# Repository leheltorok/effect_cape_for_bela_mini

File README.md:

# Effect Cape for Bela Mini

A programmable open-platform effect pedal based on the Bela framework.

The objective of this project is to create a customizable guitar effects pedal using Bela's embedded computing framework. The pedal  allows guitarists to design and run their own effects on dedicated audio hardware. To achieve this, an extension cape has been developed, integrating essential components such as rotary encoders, switches, and audio inputs/outputs onto a single circuit. Additionally, a software framework has been created using Pure Data, providing all the necessary functions for utilizing the device.

Demo Video:
https://www.youtube.com/watch?v=Ah0W3sH00xs&ab_channel=LehelTorok

## Authors and acknowledgment

Lehel Török - 2023

I would like to express my gratitude to the Bela team for providing exceptional tutorials and their invaluable support on the community forum. Additionally, I extend my thanks to the user community for generously sharing excellent code examples, which serve as a solid foundation for all of us to build upon.

## License

Creative Commons Attribution-NonCommercial-ShareAlike 4.0 International License
https://creativecommons.org/licenses/by-sa/4.0/

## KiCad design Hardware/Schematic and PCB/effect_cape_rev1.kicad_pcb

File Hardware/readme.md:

The circuit board was designed using KiCad, and manufactured with Eurocircuits. The cape was conceived as a stompbox incorporating four rotary encoders, each equipped with a switch, as well as two footswitches, all of which can be assigned based on personal preferences. The cape includes a 6.3 mm mono jack socket for audio input, two identical sockets for audio output, a 3.5 mm stereo jack socket for headphone output, and a 6.3 mm stereo jack socket for expression pedal input. In order to provide visual feedback for different modes, changes, and the status of each rotary encoder, both a bicolor LED and an OLED screen were integrated into the board. Additionally, to ensure compatibility with pedal board power supplies, a DC Barrel Jack was incorporated, enabling external power (5V/100mA) using 2.1 mm or 2.5 mm plugs with a negative polarity.

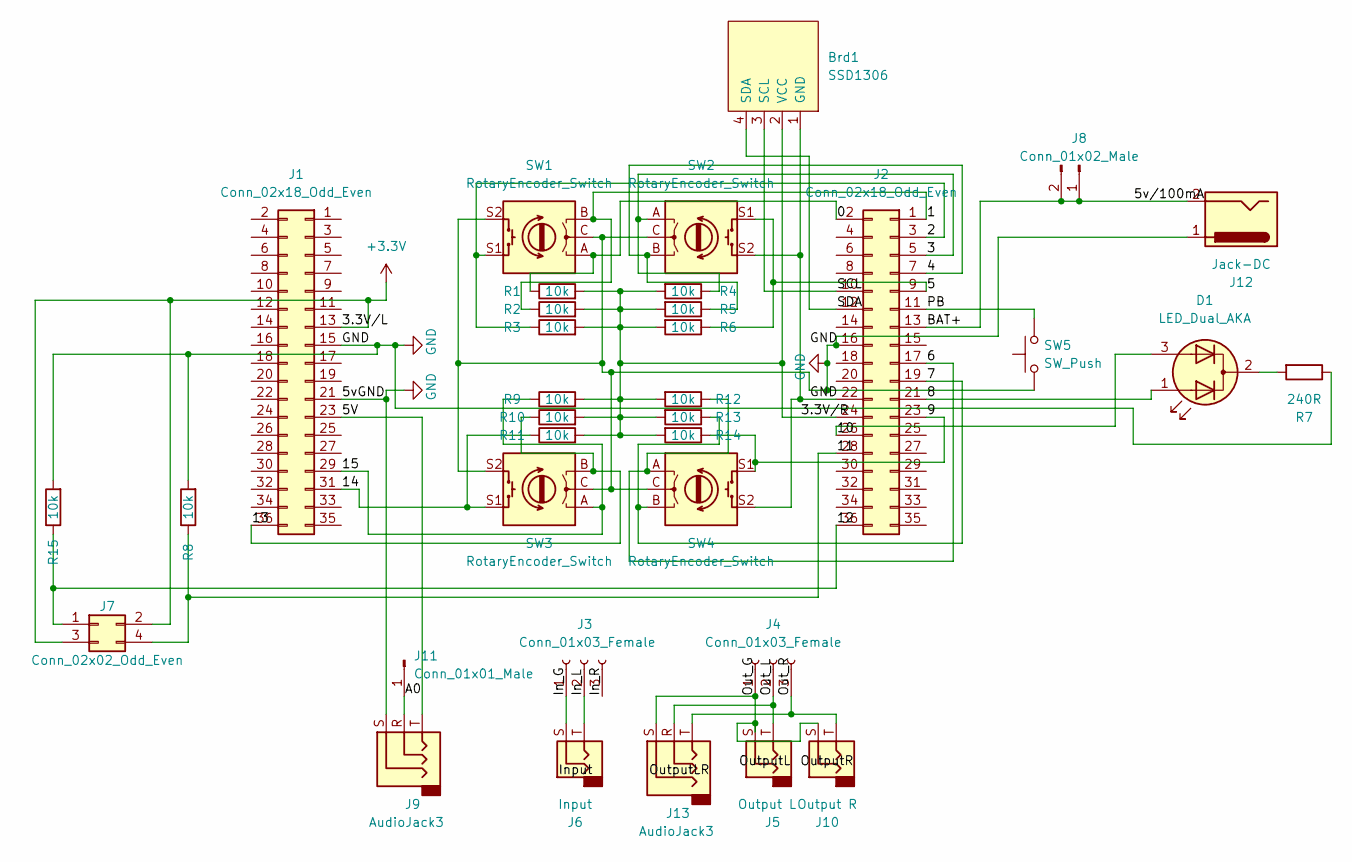
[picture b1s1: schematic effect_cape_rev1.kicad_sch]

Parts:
Brd1: SSD1306; PinSocket_1x04_P2.54mm_Vertical
D1: LED_Dual_AKA; LED_D3.0mm-3
J1, J2: Conn_02x18_Odd_Even; PinHeader_2x18_P2.54mm_Vertical
J3, J4: Conn_01x03_Female; PinSocket_1x03_P2.54mm_Vertical
J5: Output L; Jack_6.35mm_Neutrik_NRJ4HF_Horizontal
J6: Input; Jack_6.35mm_Neutrik_NRJ4HF_Horizontal
J7: Conn_02x02_Odd_Even; PinHeader_2x02_P2.54mm_Vertical
J8: Conn_01x02_Male; PinHeader_1x02_P2.54mm_Vertical
J9: AudioJack3; Jack_6.35mm_Neutrik_NRJ6HF_Horizontal
J10: Output R; Jack_6.35mm_Neutrik_NRJ4HF_Horizontal
J11: Conn_01x01_Male; PinHeader_1x01_P2.54mm_Vertical
J12: Jack-DC; BarrelJack_Horizontal
J13: AudioJack3; Jack_3.5mm_CUI_SJ1-3535NG_Horizontal
R1, R2, R3, R4, R5, R6, R8, R9, R10, R11, R12, R13, R14, R15: 10k; R_0603_1608Metric
R7: 240R; R_0603_1608Metric
SW1, SW2, SW3, SW4: RotaryEncoder_Switch; RotaryEncoder_Alps_EC11E-Switch_Vertical_H20mm
SW5: SW_Push; SW_Tactile_SPST_Angled_PTS645Vx58-2LFS

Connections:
+3V3: J1.13, J7.2, J7.3
/0: J2.2, R1.1, SW1.A
/1: J2.1, R2.1, SW1.B
/2: J2.3, R3.1, SW1.S1
/3: J2.5, R4.1, SW2.A
/3.3V/R: Brd1.2 (VCC), J2.24, R1.2, R2.2, R3.2, R4.2, R5.2, R6.2, R9.2, R10.2, R11.2, R12.2, R13.2, R14.2
/4: J2.7, R5.1, SW2.B
/5: J2.9, R6.1, SW2.S1
/5V: J1.23, J9.T
/5v/100mA: J2.13, J8.1, J8.2, J12.2
/6: J2.17, R12.1, SW4.A
/7: J2.19, R13.1, SW4.B
/8: D1.1 (A1), J2.21
/9: J2.23, R14.1, SW4.S1
/10: D1.3 (A2), J2.26
/11: J2.28, J7.4, R8.1
/12: J2.36, J7.1, R15.1
/13: J1.36, R10.1, SW3.B
/14: J1.31, R11.1, SW3.S1
/15: J1.29, R9.1, SW3.A
/A0: J9.R, J11.1
/In_G: J3.1, J6.S
/In_L: J3.2, J6.T
/In_R: J3.3
/Out_G: J4.1, J5.S, J10.S, J13.S; also elsewhere on the board
/Out_L: J4.2, J5.T, J13.R; also elsewhere on the board
/Out_R: J4.3, J10.T, J13.T; also elsewhere on the board
/PB: J2.11, SW5.2
/SCL: Brd1.3 (SCL), J2.10
/SDA: Brd1.4 (SDA), J2.12
GND: Brd1.1 (GND), J1.15, J1.21, J2.16, J2.22, J9.S, J12.1, R7.1, R8.2, R15.2, SW1.C, SW1.S2, SW2.C, SW2.S2, SW3.C, SW3.S2, SW4.C, SW4.S2, SW5.1
unnamed: D1.2 (K), R7.2

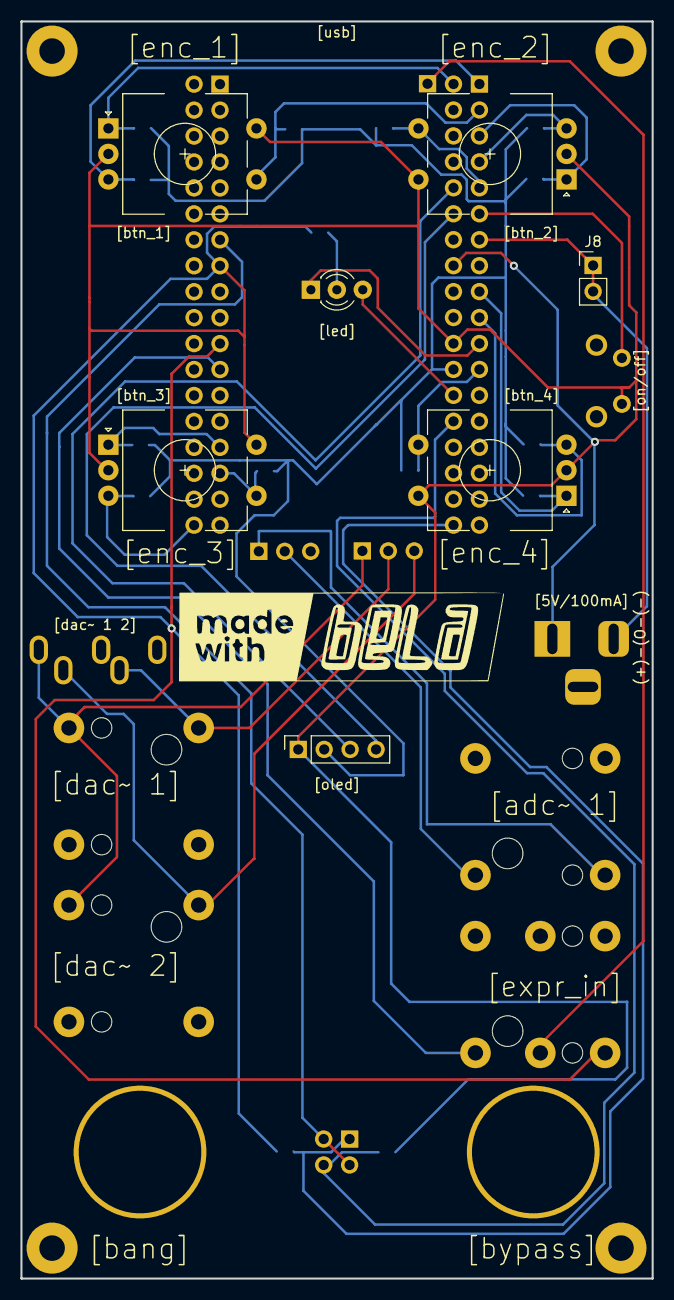
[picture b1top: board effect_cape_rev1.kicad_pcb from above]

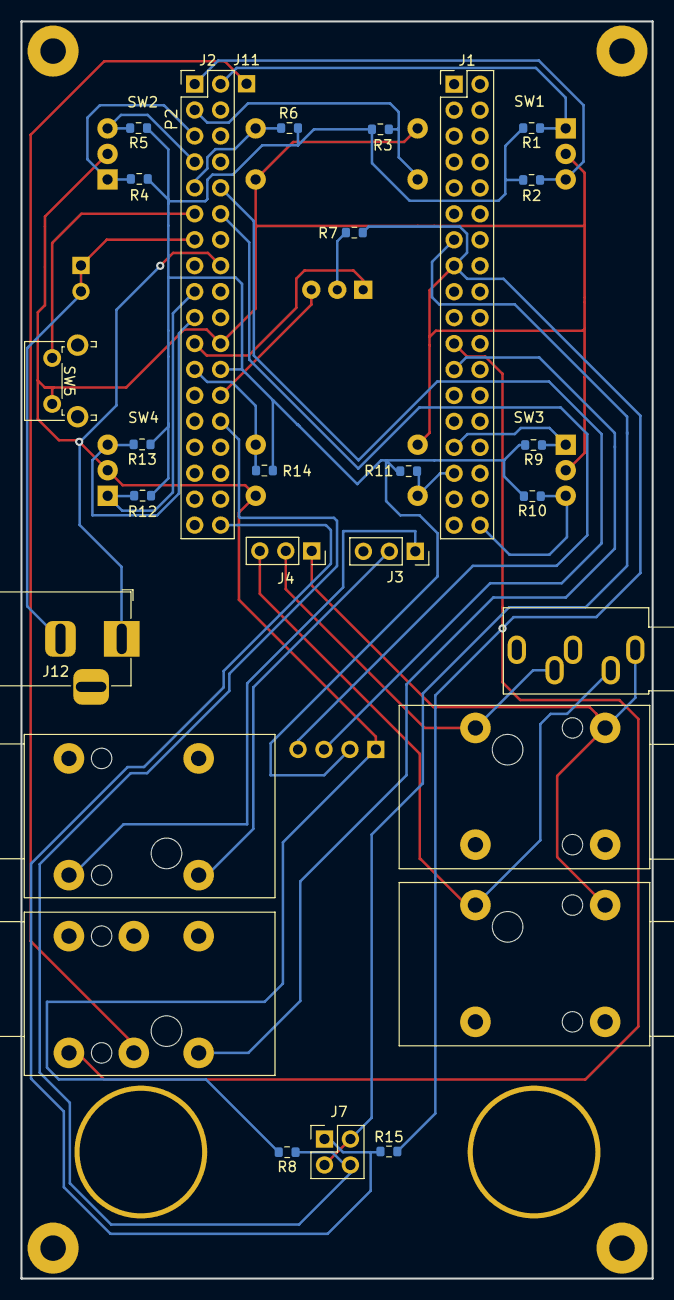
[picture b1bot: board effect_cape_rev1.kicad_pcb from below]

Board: 2 copper layers, 61.8 x 123.1 mm, 42 parts (28 on the bottom side), 31 nets.

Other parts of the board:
G: LOGO; madewithbela
Headphone Output (Stereo): AudioJack3; Jack_3.5mm_CUI_SJ1-3535NG_Horizontal
Momentary Footswitch: PF4520
Momentary Footswitch#2: PF4520
Mounting Hole: 2.5mm
Mounting Hole#2, Mounting Hole#3, Mounting Hole#4: 2.5mm

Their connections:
/Out_G: Headphone Output (Stereo).S; also elsewhere on the board
/Out_L: Headphone Output (Stereo).R; also elsewhere on the board
/Out_R: Headphone Output (Stereo).T; also elsewhere on the board

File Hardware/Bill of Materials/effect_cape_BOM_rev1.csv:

NAME,VALUE,FOOTPRINT,QUANTITY,LINK
"R1, R2, R3, R4, R5, R6, R8, R9, R10, R11, R12, R13, R14, R15",10k,R_0603_1608Metric,14,https://www.reichelt.at/de/en/smd-chip-resistor-0603-10-kohm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
R7,240R,R_0603_1608Metric,1,https://www.reichelt.at/de/en/smd-chip-resistor-0603-220-ohm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
SW,SW_Push,SW_Tactile_SPST_Angled_PTS645Vx58-2LFS,1,https://www.reichelt.at/de/en/short-stroke-key-6-6x7-4-mm-he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
"Enc_1, Enc_2, Enc_3, Enc_4",RotaryEncoder_Switch,RotaryEncoder_Alps_EC11E-Switch_Vertical_H20mm,4,https://www.reichelt.at/de/en/alps-stec12e-rotary-pulse-enco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
"Input Left (Mono), Output Left, Output Right",NEUTRIK NR-J4HF,Jack_6.35mm_Neutrik_NRJ4HF_Horizontal,3,https://www.reichelt.at/de/en/neutrik-jack-socket-6-35-mm-mo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
"Momentary Footswitch, Momentary Footswitch",Thomann PF4520 ,,2,https://www.thomann.de/gb/thomann_fusstaster.htm
Expression Pedal Input,NEUTRIK NR-J6HF,Jack_6.35mm_Neutrik_NRJ6HF_Horizontal,1,https://www.reichelt.at/de/en/neutrik-jack-socket-6-35-mm-st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
Headphone Output (Stereo),CUI Devices SJ1-3535NG,Jack_3.5mm_CUI_SJ1-3535NG_Horizontal,1,https://www.mouser.co.uk/ProductDetail/CUI-Devices/SJ1-3535N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
LED Blue/Red,LED_Dual_AKA,LED_D3.0mm-3,1,https://www.tme.eu/ro/en/details/osrbmc5b31a/tht-leds-round/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
OLED,SSD1306,,1,https://arduino-projekte.info/produkt/0-96%e2%80%b3-oled-dis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
"J1, J2",Conn_02x18_Odd_Even,PinHeader_2x18_P2.54mm_Vertical,2,https://www.mouser.co.uk/ProductDetail/Wurth-Elektronik/6130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
"J3, J4",Conn_01x03_Female,PinSocket_1x03_P2.54mm_Vertical,2,https://www.reichelt.at/de/en/sockets-2-54-mm-1x03-straight-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
J7,Conn_02x02_Odd_Even,PinHeader_2x02_P2.54mm_Vertical,1,https://www.reichelt.at/de/en/pin-headers-2-54-mm-2x02-strai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
J11,Conn_01x01_Male,PinHeader_1x01_P2.54mm_Vertical,1,https://www.reichelt.at/de/en/pin-headers-2-54-mm-1x02-strai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
J12,Jack-DC,BarrelJack_Horizontal,1,https://www.reichelt.at/de/en/built-in-coupling-solder-lugs-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

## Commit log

2023-05-23 Add new file
2023-05-23 Add new directory
2023-05-23 Upload New File
2023-05-23 Update Interactive BOM
2023-05-23 Update Link
2023-05-23 Replace Delay_Chain.zip
2023-05-24 Replace _main.pd
2023-05-24 Replace interface.pd
2023-05-25 Replace Routing_diagram.jpg
2023-06-22 Create Case
2023-06-24 Add files via upload
    Modified [encoder_in] and introduced [latency_fix] to enhance the speed at which value changes are displayed on the OLED screen.
2023-07-31 Add files via upload
    Updated render.cpp file to newest version.
